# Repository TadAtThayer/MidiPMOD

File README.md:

#MidiPMOD

This is a tiny little board which converts a standard MiDi (current mode) signal to CMOS levels
suitable for use with the Xilinx Artix-7 FPGA on the Digilent Basys-3 board.

The MiDi port is opto-isolated from the FPGA side.

This board can be manufactired in nearly any proces.

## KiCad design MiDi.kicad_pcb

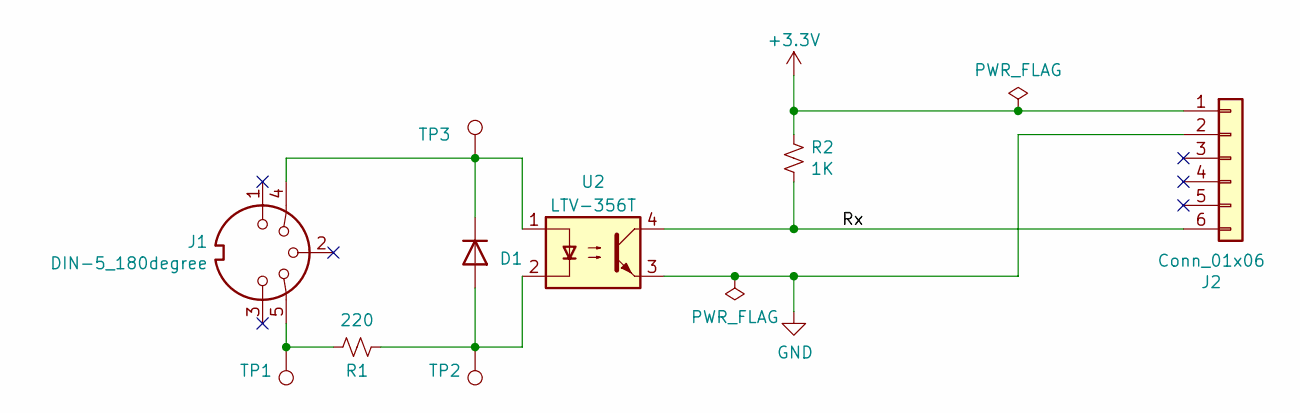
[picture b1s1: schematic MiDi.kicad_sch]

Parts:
D1: RF01VM2S; D_0603_1608Metric
J1: DIN-5_180degree; CUI_SDS-50J
J2: Conn_01x06; PinHeader_1x06_P2.54mm_Horizontal
R1: 220; R_0603_1608Metric
R2: 1K; R_0603_1608Metric
TP1, TP2, TP3: TestPoint; TestPoint_THTPad_D1.0mm_Drill0.5mm
U2: LTV-356T; SO-4_4.4x3.6mm_P2.54mm

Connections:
+3.3V: J2.1, R2.1
/Rx: J2.6, R2.2, U2.4
GND: J2.2, U2.3
unnamed: D1.2 (A), R1.1, TP2.1, U2.2
unnamed: D1.1 (K), J1.4, TP3.1, U2.1
unnamed: J1.5, R1.2, TP1.1

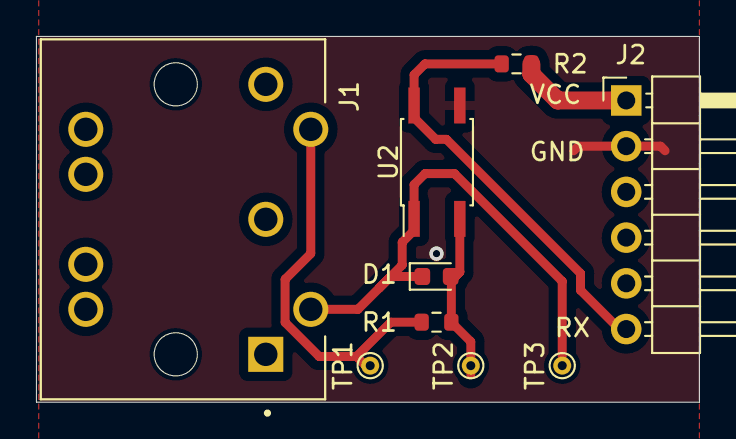
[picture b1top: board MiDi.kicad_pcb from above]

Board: 2 copper layers, 36.8 x 20.3 mm, 9 parts (0 on the bottom side), 6 nets.

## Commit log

2023-05-25 initial midi board
2023-05-25 fix some drcs
2023-05-25 add v1 QR code
2023-05-25 Add gerber zip sent to OSHPark
2023-06-24 V1.1
    ChangeList
    1) Reduce width to 0.8"
    2) Reduce TP size (to 0.5mm) move inside edge cut
    3) Move J2 closer to edge cut
    4) Change Diode footprint to 603. Old ?SMD_323? was too prone to
    tombstoning
2023-08-14 Modify DIN5 footprint file to work with both prevalent styles of DIN5 connector
2025-04-06 add readme
2026-03-22 reorg
2026-03-22 start neo-pixel pmod
2026-03-23 work on schematic

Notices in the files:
MiDi.kicad_pcb:
Copyright 2023
